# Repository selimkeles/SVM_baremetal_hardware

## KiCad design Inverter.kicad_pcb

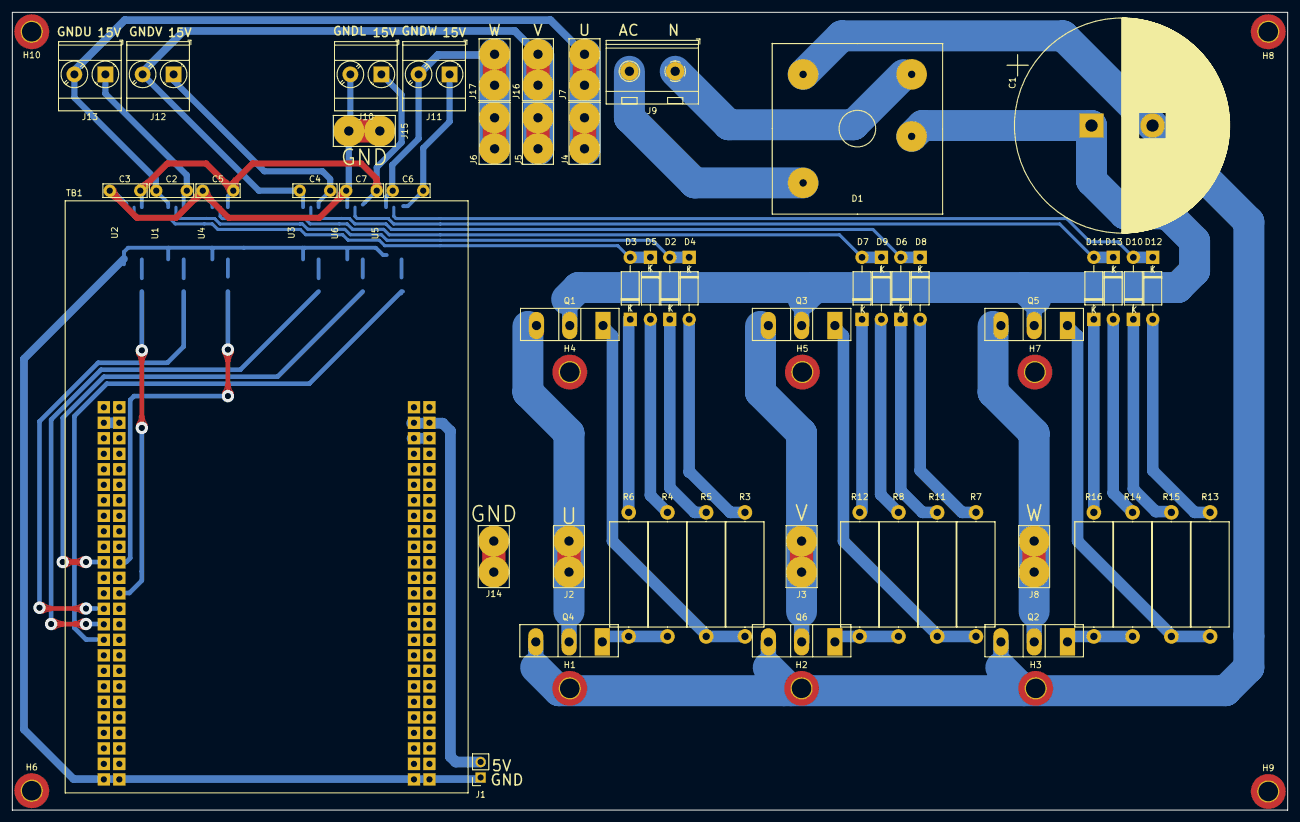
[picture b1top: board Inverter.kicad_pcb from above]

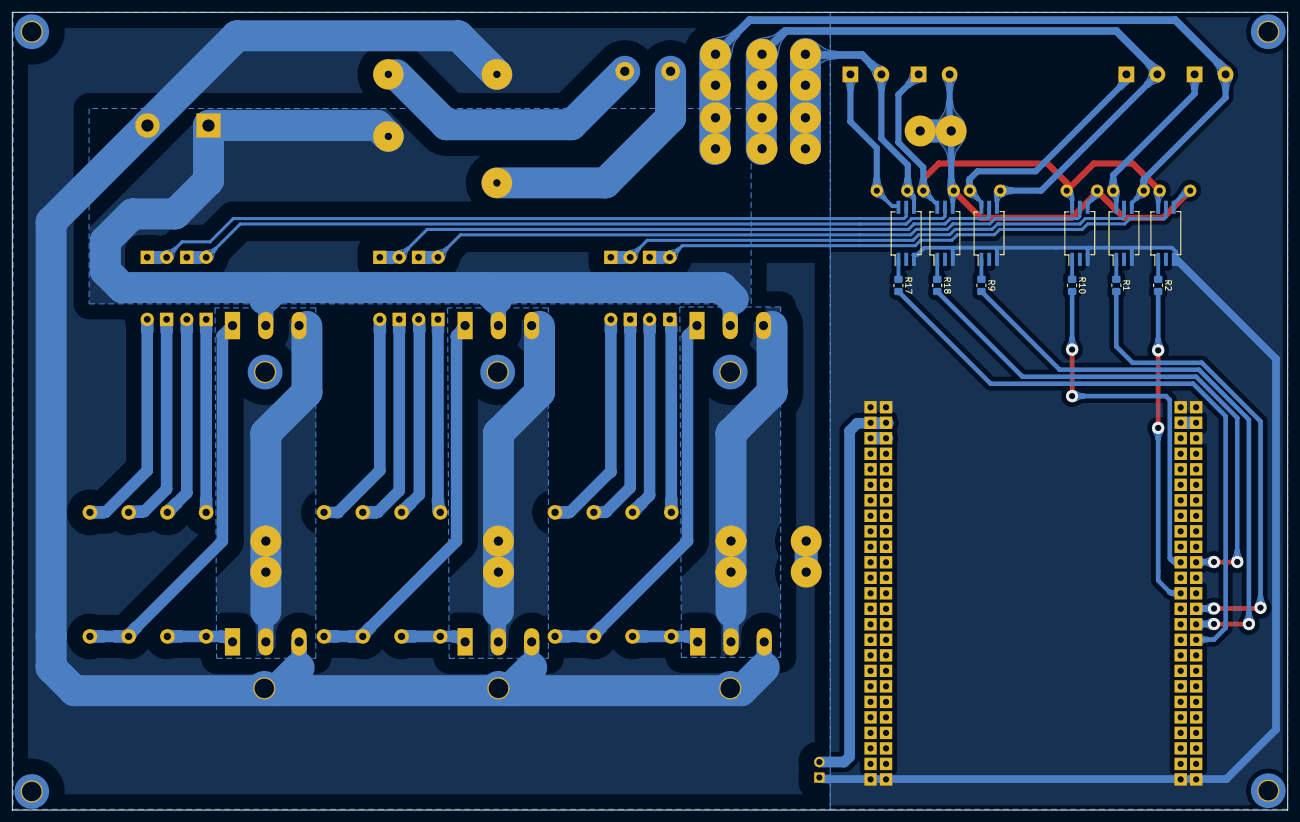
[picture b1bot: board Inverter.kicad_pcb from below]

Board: 2 copper layers, 208.9 x 130.7 mm, 78 parts (12 on the bottom side), 51 nets.

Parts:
C1: 750uF; CP_Radial_D35.0mm_P10.00mm_SnapIn
C2, C3, C4, C5, C6, C7: 0.1uF; C_Rect_L7.0mm_W2.0mm_P5.00mm
D1: CD2320-B11000_Obsolete; KBPC3510W
D2, D3, D4, D5, D6, D7, D8, D9, D10, D11, D12, D13: D_Schottky_Small; D_DO-41_SOD81_P10.16mm_Horizontal
H1, H2, H3: MountingHole_Pad; MountingHole_3.2mm_M3_ISO7380_Pad_TopBottom
H4, H5, H6, H7, H8, H9, H10: MountingHole; MountingHole_3.2mm_M3_ISO7380_Pad_TopBottom
J1: Screw_Terminal_01x02; PinSocket_1x02_P2.54mm_Vertical
J2, J3, J4, J5, J6, J7, J8, J14, J15, J16, J17: QuickConnector
J9: Screw_Terminal_01x02; 2POS_7.5mm
J10, J11, J12, J13: Screw_Terminal_01x02; TerminalBlock_Phoenix_MKDS-3-2-5.08_1x02_P5.08mm_Horizontal
Q1, Q2, Q3, Q4, Q5, Q6: STGP7NC60HD; TO-247-3_Vertical
R1, R2, R9, R10, R17, R18: 2K; R_0805_2012Metric_Pad1.20x1.40mm_HandSolder
R3, R4, R7, R8, R13, R14: 10R; R_Axial_DIN0617_L17.0mm_D6.0mm_P20.32mm_Horizontal
R5, R6, R11, R12, R15, R16: 1K; R_Axial_DIN0617_L17.0mm_D6.0mm_P20.32mm_Horizontal
TB1: STM32F4DISCOVERY; MODULE_STM32F4DISCOVERY
U1, U2, U3, U4, U5, U6: IS314W; SSO-6_6.8x4.6mm_P1.27mm_Clearance7mm

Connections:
+3V3: TB1.P1_3, TB1.P1_4, TB1.P2_22
+VDC: C1.1, D1.4, Q1.2, Q3.2, Q5.2
/PWM_HU: R1.2, TB1.P1_27
/PWM_HV: R9.2, TB1.P1_29
/PWM_HW: R17.2, TB1.P1_31
/PWM_I_HU: D2.2, D4.1, U1.5
/PWM_I_HV: D6.2, D8.1, U3.5
/PWM_I_HW: D10.2, D12.1, U5.5
/PWM_I_LU: D3.2, D5.1, U2.5
/PWM_I_LV: D7.2, D9.1, U4.5
/PWM_I_LW: D11.2, D13.1, U6.5
/PWM_LU: R2.2, TB1.P1_26
/PWM_LV: R10.2, TB1.P1_22
/PWM_LW: R18.2, TB1.P1_21
AC: D1.1, J9.2
GND_L: C1.2, C3.2, C5.2, C7.2, D1.3, H1.1, H2.1, H3.1, J10.2, J14.1, J15.1, Q2.3, Q4.3, Q6.3, U2.4, U4.4, U6.4
GND_MCU: J1.1, TB1.P1_1, TB1.P1_2, TB1.P1_5, TB1.P1_23, TB1.P1_49, TB1.P1_50, TB1.P2_1, TB1.P2_2, TB1.P2_49, TB1.P2_50, U1.3, U2.3, U3.3, U4.3, U5.3, U6.3
GND_U: C2.2, J2.1, J4.1, J7.1, J13.2, Q1.3, Q4.2, U1.4
GND_V: C4.2, J3.1, J5.1, J12.2, J16.1, Q3.3, Q6.2, U3.4
GND_W: C6.2, J6.1, J8.1, J11.2, J17.1, Q2.2, Q5.3, U5.4
NEUT: D1.2, J9.1
unnamed: D2.1, R5.2
unnamed: D3.1, R6.2
unnamed: D4.2, R3.2
unnamed: D5.2, R4.2
unnamed: D6.1, R11.2
unnamed: D7.1, R12.2
unnamed: D8.2, R7.2
unnamed: D9.2, R8.2
unnamed: D10.1, R15.2
unnamed: D11.1, R16.2
unnamed: D12.2, R13.2
unnamed: D13.2, R14.2
unnamed: Q1.1, R3.1, R5.1
unnamed: Q2.1, R14.1, R16.1
unnamed: Q3.1, R7.1, R11.1
unnamed: Q4.1, R4.1, R6.1
unnamed: Q5.1, R13.1, R15.1
unnamed: Q6.1, R8.1, R12.1
unnamed: R1.1, U1.1
unnamed: R2.1, U2.1
unnamed: R9.1, U3.1
unnamed: R10.1, U4.1
unnamed: R17.1, U5.1
unnamed: R18.1, U6.1
unnamed: TB1.P2_5, TB1.P2_6
Power_L: C3.1, C5.1, C7.1, J10.1, U2.6, U4.6, U6.6
Power_MCU: J1.2, TB1.P2_3, TB1.P2_4
Power_U: C2.1, J13.1, U1.6
Power_V: C4.1, J12.1, U3.6
Power_W: C6.1, J11.1, U5.6

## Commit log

2026-02-27 dev: added gitignore and core of kicad 9 filesystem
2026-02-27 added local lib as module
2026-04-19 dev: added NC flags and fixed ERC warnings. Added custom design rules for PCB Design.
